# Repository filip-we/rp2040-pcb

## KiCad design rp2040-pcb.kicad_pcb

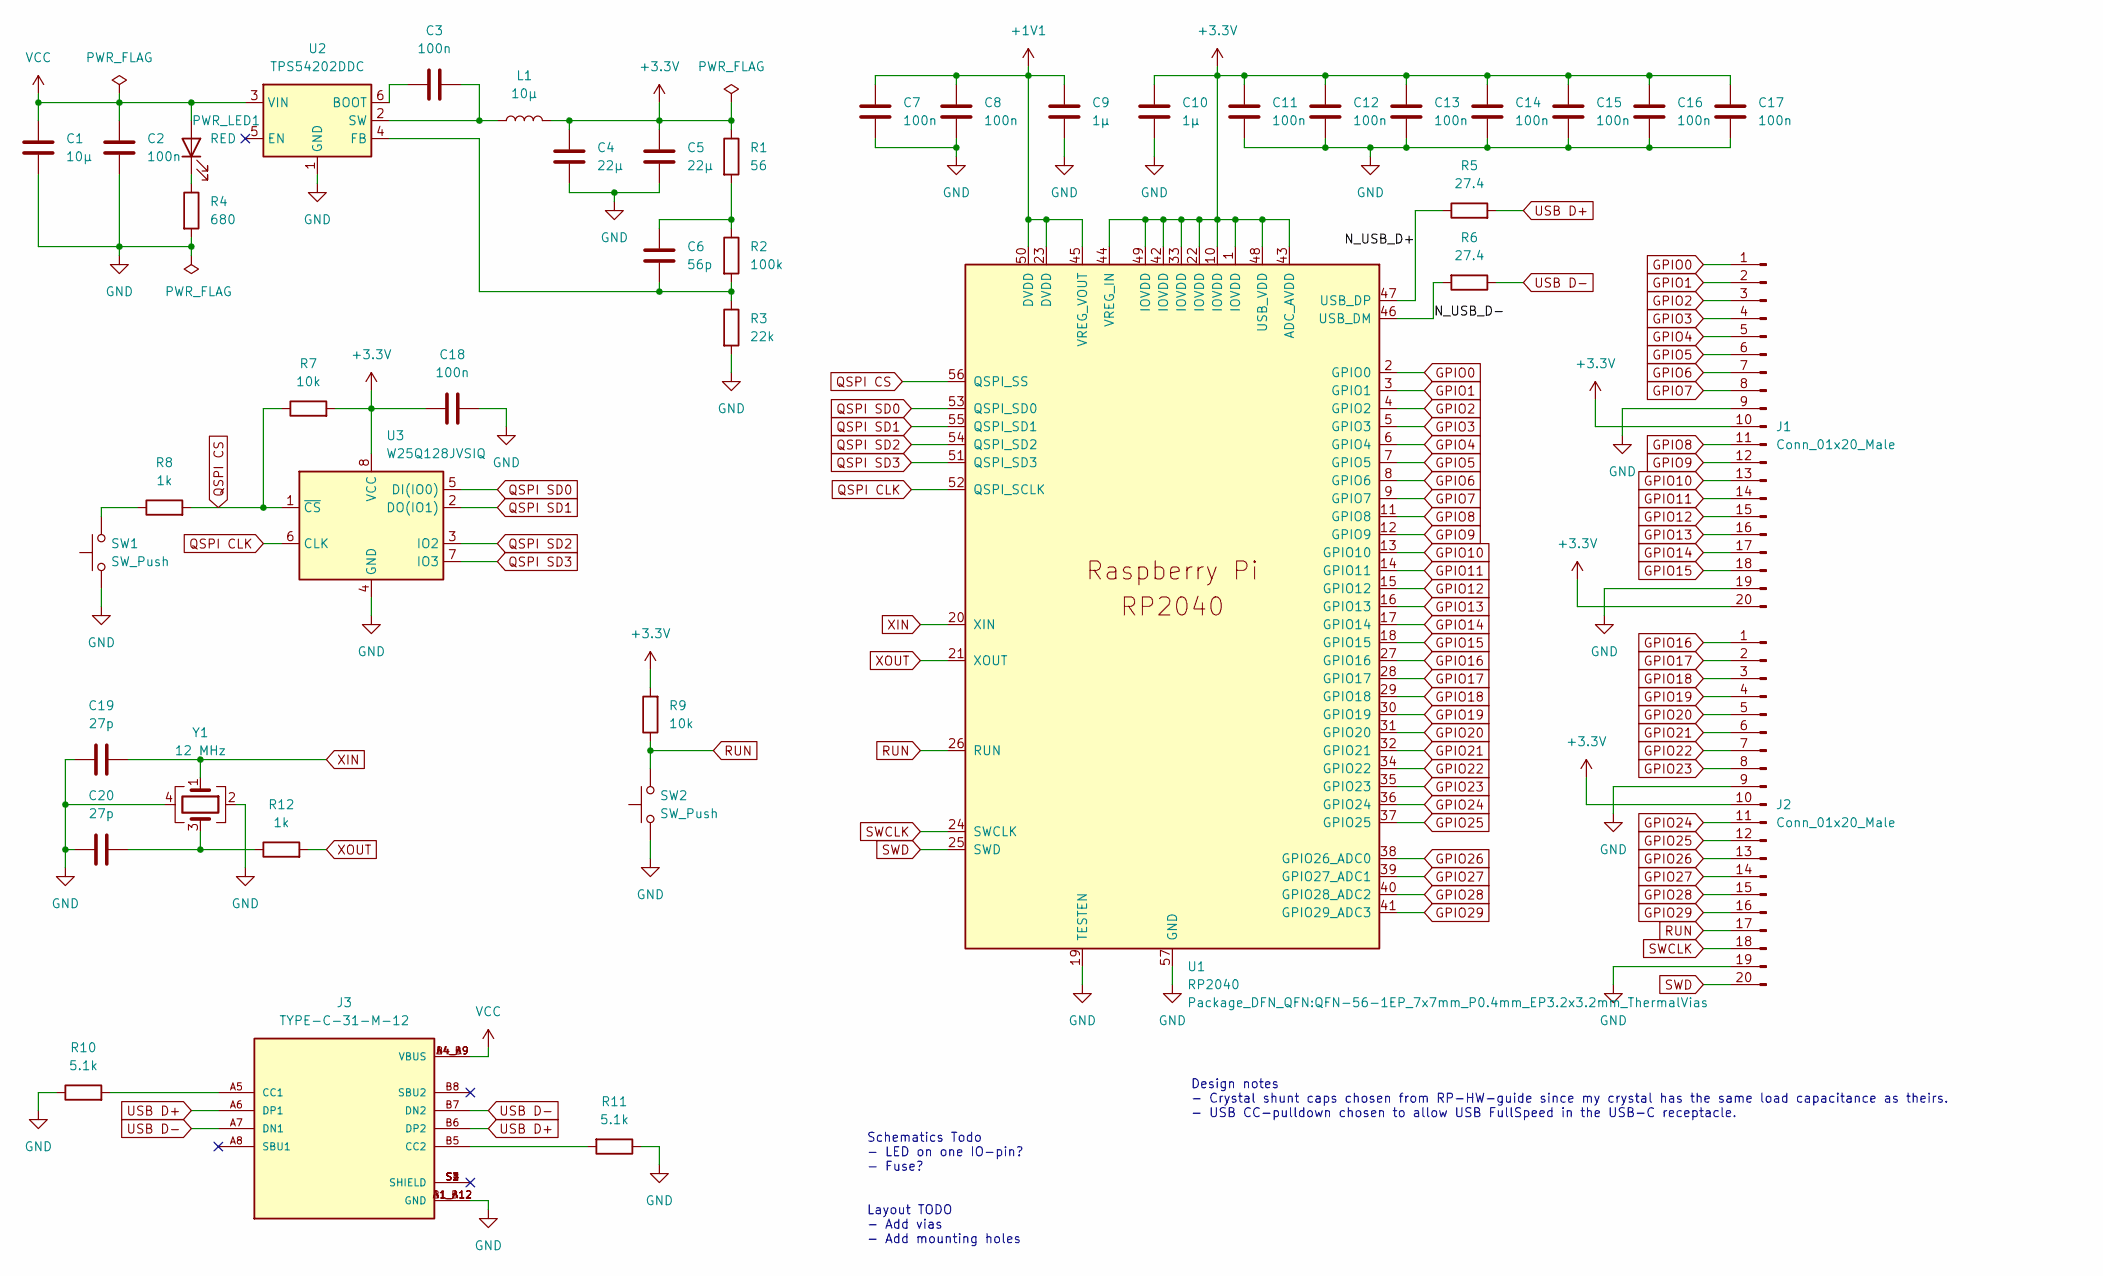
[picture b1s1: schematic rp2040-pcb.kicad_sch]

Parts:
C1: 10µ; C_0603_1608Metric
C2, C3, C7, C8, C11, C12, C13, C14, C15, C16, C17, C18: 100n; C_0402_1005Metric
C4, C5: 22µ; C_0805_2012Metric
C6: 56p; C_0402_1005Metric
C9, C10: 1µ; C_0603_1608Metric
C19, C20: 27p; C_0402_1005Metric
J1, J2: Conn_01x20_Male; PinHeader_1x20_P2.54mm_Vertical
J3: TYPE-C-31-M-12; HRO_TYPE-C-31-M-12; PARTREV 2020.12.08
L1: 10µ; L_0603_1608Metric
PWR_LED1: RED; LED_0805_2012Metric; Fwd Voltage 2 V
R1: 56; R_0402_1005Metric
R2: 100k; R_0402_1005Metric
R3: 22k; R_0402_1005Metric
R4: 680; R_0402_1005Metric
R5, R6: 27.4; R_0402_1005Metric
R7, R9: 10k; R_0402_1005Metric
R8, R12: 1k; R_0402_1005Metric
R10, R11: 5.1k; R_0402_1005Metric
SW1, SW2: SW_Push; SW_SPST_TL3342
U1: RP2040; QFN-56-1EP_7x7mm_P0.4mm_EP3.2x3.2mm_ThermalVias
U2: TPS54202DDC; SOT-23-6
U3: W25Q128JVSIQ; SOIC-8_5.23x5.23mm_P1.27mm
Y1: 12 MHz; Oscillator_SMD_EuroQuartz_XO32-4Pin_3.2x2.5mm

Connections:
+1V1: C7.1, C8.1, C9.1, U1.23 (DVDD), U1.45 (VREG_VOUT), U1.50 (DVDD)
+3.3V: C4.1, C5.1, C10.1, C11.1, C12.1, C13.1, C14.1, C15.1, C16.1, C17.1, C18.2, J1.10, J1.20, J2.10, L1.2, R1.1, R7.2, R9.2, U1.1 (IOVDD), U1.10 (IOVDD), U1.22 (IOVDD), U1.33 (IOVDD), U1.42 (IOVDD), U1.43 (ADC_AVDD), U1.44 (VREG_IN), U1.48 (USB_VDD), U1.49 (IOVDD), U3.8 (VCC)
/N_USB_D+: R5.1, U1.47 (USB_DP)
/N_USB_D-: R6.2, U1.46 (USB_DM)
GND: C1.2, C2.2, C4.2, C5.2, C7.2, C8.2, C9.2, C10.2, C11.2, C12.2, C13.2, C14.2, C15.2, C16.2, C17.2, C18.1, C19.1, C20.1, J1.9, J1.19, J2.9, J2.19, J3.A1_B12 (GND), J3.B1_A12 (GND), R3.2, R4.2, R10.1, R11.1, SW1.1, SW2.1, U1.19 (TESTEN), U1.57 (GND), U2.1 (GND), U3.4 (GND), Y1.2, Y1.4
GPIO0: J1.1, U1.2 (GPIO0)
GPIO1: J1.2, U1.3 (GPIO1)
GPIO2: J1.3, U1.4 (GPIO2)
GPIO3: J1.4, U1.5 (GPIO3)
GPIO4: J1.5, U1.6 (GPIO4)
GPIO5: J1.6, U1.7 (GPIO5)
GPIO6: J1.7, U1.8 (GPIO6)
GPIO7: J1.8, U1.9 (GPIO7)
GPIO8: J1.11, U1.11 (GPIO8)
GPIO9: J1.12, U1.12 (GPIO9)
GPIO10: J1.13, U1.13 (GPIO10)
GPIO11: J1.14, U1.14 (GPIO11)
GPIO12: J1.15, U1.15 (GPIO12)
GPIO13: J1.16, U1.16 (GPIO13)
GPIO14: J1.17, U1.17 (GPIO14)
GPIO15: J1.18, U1.18 (GPIO15)
GPIO16: J2.1, U1.27 (GPIO16)
GPIO17: J2.2, U1.28 (GPIO17)
GPIO18: J2.3, U1.29 (GPIO18)
GPIO19: J2.4, U1.30 (GPIO19)
GPIO20: J2.5, U1.31 (GPIO20)
GPIO21: J2.6, U1.32 (GPIO21)
GPIO22: J2.7, U1.34 (GPIO22)
GPIO23: J2.8, U1.35 (GPIO23)
GPIO24: J2.11, U1.36 (GPIO24)
GPIO25: J2.12, U1.37 (GPIO25)
GPIO26: J2.13, U1.38 (GPIO26_ADC0)
GPIO27: J2.14, U1.39 (GPIO27_ADC1)
GPIO28: J2.15, U1.40 (GPIO28_ADC2)
GPIO29: J2.16, U1.41 (GPIO29_ADC3)
unnamed: C3.1, L1.1, U2.2 (SW)
unnamed: C3.2, U2.6 (BOOT)
unnamed: C6.1, R1.2, R2.1
unnamed: C6.2, R2.2, R3.1, U2.4 (FB)
unnamed: C20.2, R12.1, Y1.3
unnamed: PWR_LED1.1 (K), R4.1
unnamed: R8.1, SW1.2
unnamed: J3.A5 (CC1), R10.2
unnamed: J3.B5 (CC2), R11.2
QSPI CLK: U1.52 (QSPI_SCLK), U3.6 (CLK)
QSPI CS: R7.1, R8.2, U1.56 (QSPI_SS), U3.1 (~CS)
QSPI SD0: U1.53 (QSPI_SD0), U3.5 (DI(IO0))
QSPI SD1: U1.55 (QSPI_SD1), U3.2 (DO(IO1))
QSPI SD2: U1.54 (QSPI_SD2), U3.3 (IO2)
QSPI SD3: U1.51 (QSPI_SD3), U3.7 (IO3)
RUN: J2.17, R9.1, SW2.2, U1.26 (RUN)
SWCLK: J2.18, U1.24 (SWCLK)
SWD: J2.20, U1.25 (SWD)
USB D+: J3.A6 (DP1), J3.B6 (DP2), R5.2
USB D-: J3.A7 (DN1), J3.B7 (DN2), R6.1
VCC: C1.1, C2.1, J3.A4_B9 (VBUS), J3.B4_A9 (VBUS), PWR_LED1.2 (A), U2.3 (VIN)
XIN: C19.2, U1.20 (XIN), Y1.1
XOUT: R12.2, U1.21 (XOUT)

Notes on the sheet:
Schematics Todo - LED on one IO-pin? - Fuse? Layout TODO - Add vias - Add mounting holes
Design notes - Crystal shunt caps chosen from RP-HW-guide since my crystal has the same load capacitance as theirs. - USB CC-pulldown chosen to allow USB FullSpeed in the USB-C receptacle.

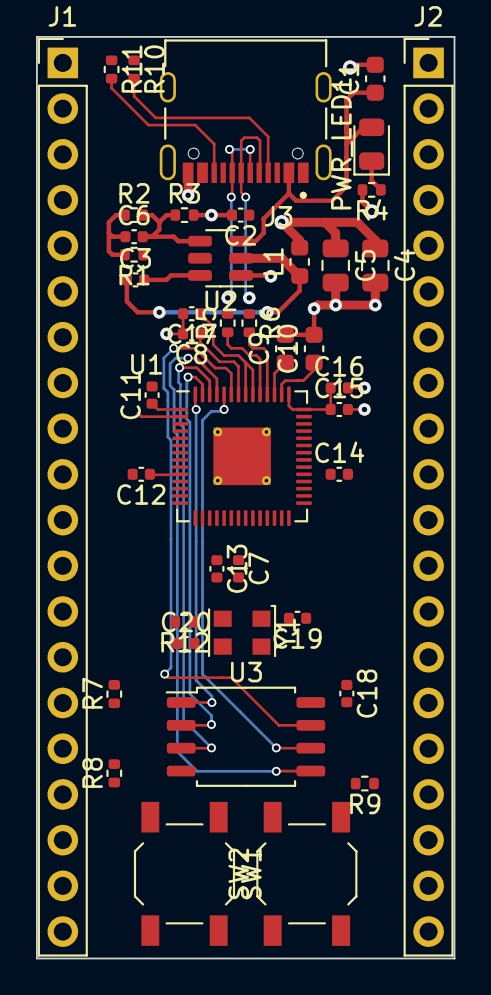
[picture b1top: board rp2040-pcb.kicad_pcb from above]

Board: 2 copper layers, 23.2 x 51.2 mm, 43 parts (0 on the bottom side), 58 nets.

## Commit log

2023-02-28 Added buck converter.
2023-03-01 Added SPI-memory.
2023-03-10 Added USB, RP2040 and decoupling caps.
2023-03-11 Added IO-header-pins.
2023-03-11 Added reset-button.
2023-03-12 Added power LED.
2023-03-12 Fixed missed resistor in voltage regulator.
2023-03-12 Added annotations.
2023-03-12 Added footprints to all components.
2023-03-14 Addressed electrical rules check-errors.
2023-03-16 Exchanged USB-receptacle. I could not find a footprint for the Chinese USB-receptacle I had chosen. Thus I selected one from Molex instead.
2023-03-16 Generated net list
2023-03-16 Started routing.
2023-03-19 Moved components roughly in place.
2023-03-19 Updated numbering. Updated USB footpring on PCB.
2023-03-19 Aligned RP and headers.
2023-03-19 Board outline
2023-03-19 more components placed
2023-03-19 Changed USB-receptacle again.
2023-03-19 Routed USB.
2023-03-24 Made board a bit bigger.
2023-03-24 removed backups
2023-03-25 Routed voltage regulator.
2023-03-25 Routed even more
